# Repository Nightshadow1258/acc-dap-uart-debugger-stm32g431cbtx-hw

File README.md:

# ACC DAP-UART Debugger (STM32G431) – Hardware

A small, low-cost **USB-C debug probe** that combines a **CMSIS-DAP (SWD) debugger** and a **USB-to-UART bridge** in a single USB device. It connects to the target with a 10-pin **Tag-Connect TC2050** cable.

When plugged into a PC, the board shows up as:
- a **CMSIS-DAP v2 probe** (works with OpenOCD, `west flash`, `west debug`, GDB)
- a **virtual COM port** (USB CDC-ACM) that forwards the target's UART

One cable to the PC, one cable to the target.

> **Firmware:** this repository only contains the hardware. The Zephyr RTOS firmware is here:
> [acc-dap-uart-debugger-stm32g431cbtx-fw](https://github.com/Nightshadow1258/acc-dap-uart-debugger-stm32g431cbtx-fw)
>
> **Blog post:** [DIY Debugger: CMSIS-DAP + UART over a Single USB-C Cable](https://blog.preisch.cloud/) <!-- TODO: replace with the post's URL once published -->

---

## Features

| | |
|---|---|
| **MCU** | STM32G431CBT6 (Cortex-M4, 170 MHz, 128 KB Flash, 32 KB RAM, LQFP48) |
| **USB** | USB Type-C, USB 2.0 Full-Speed, crystal-less (internal HSI48) |
| **Power** | Bus-powered from USB 5 V, no external supply |
| **Debug interface** | SWD (SWCLK, SWDIO, NRST) via bit-banged GPIO |
| **UART bridge** | USART2, default 115200 baud |
| **Target connector** | Tag-Connect TC2050 (10-pin, no header needed on the target) |
| **Indicators** | Power LED, status LED |
| **Enclosure** | Two-part 3D-printable case (FreeCAD) |

---

## Repository Structure

```
ACC_DAP-UART-Debugger_STM32G431CBTx/
├── Dokumentation/   # Schematic PDF, images, notes
├── KiCAD/           # KiCad project (ACC_DAP-UART-Debugger_STM32G431CBTx.kicad_pro)
└── FreeCAD/         # Enclosure design (top + bottom part)
```

---

## Target Connector Pinout (TC2050)

Pin names are from the **target MCU's side**.

| Pin Name   | Pin | Pin | Pin Name   |
|------------|:---:|:---:|------------|
| VDD        | 1   | 2   | GND        |
| UART_RXD   | 3   | 4   | UART_TXD   |
| JTMS_SWDIO | 5   | 6   | JTCK_SWCLK |
| JTDO_SWO   | 7   | 8   | JTDI       |
| TBD/Free   | 9   | 10  | JTRST      |

- The target's `UART_RXD` (pin 3) connects to the debugger's **TX**, and the target's `UART_TXD` (pin 4) to the debugger's **RX**.
- Pin 9 is reserved for future use.
- This debugger uses **SWD only**. The JTAG-only pins (`JTDI`, `JTRST`) and `SWO` are part of the connector standard but not used by the current firmware.

To use the debugger with your own board, place the **TC2050-IDC-NL** footprint (no-legs version, or the legged version for retention clips) and route it according to the table above.

---

## MCU Pin Assignment

| Function | MCU Pin | Notes |
|---|---|---|
| Target SWCLK | `PA5` | GPIO, push-pull |
| Target SWDIO | `PA4` | GPIO, pull-up |
| Target NRST  | `PB0` | GPIO |
| Target UART TX | `PA2` | USART2_TX |
| Target UART RX | `PA3` | USART2_RX |
| USB D- / D+ | `PA11` / `PA12` | USB FS |

---

## Enclosure

The case was designed in **FreeCAD** around the STEP model exported from KiCad.

- Two parts (top + bottom)
- Screws go in from the bottom and sit in recessed mounting points
- The top part holds **M2 threaded inserts** and has a cut-out for the TC2050 connector

---

## Getting Started

1. **Order / assemble** the PCB from the files in `KiCAD/`.
2. **Flash the firmware** over USB DFU (STM32 ROM bootloader):
   - hold `BOOT0`, plug in USB, release `BOOT0`
   - flash using the instructions in the [firmware repository](https://github.com/Nightshadow1258/acc-dap-uart-debugger-stm32g431cbtx-fw)
3. **Connect** the TC2050 cable to your target and check that the probe is detected:
   ```bash
   openocd -f interface/cmsis-dap.cfg -f target/stm32f4x.cfg
   ```
4. **Use it in a Zephyr project** by adding this to the target's `board.cmake`:
   ```cmake
   board_runner_args(openocd --config interface/cmsis-dap.cfg --config target/<target>.cfg)
   ```
   then run `west flash --runner openocd`.

### Tested targets
| Target | Status |
|---|---|
| STM32F4 ([Stepper Controller V1.0](https://blog.preisch.cloud/stepper-controller-v1-0/)) | Working |
| nRF52840 ([Sensor Node](https://blog.preisch.cloud/blog-sensor-node-v4-00/)) | Working |
| STM32G4 ([Motor Controller](https://blog.preisch.cloud/diy-motor-controller-part-i-hardware-design-bringup/)), incl. external flash | To test |

---

## License
This hardware design is licensed under the CERN-OHL-P v2

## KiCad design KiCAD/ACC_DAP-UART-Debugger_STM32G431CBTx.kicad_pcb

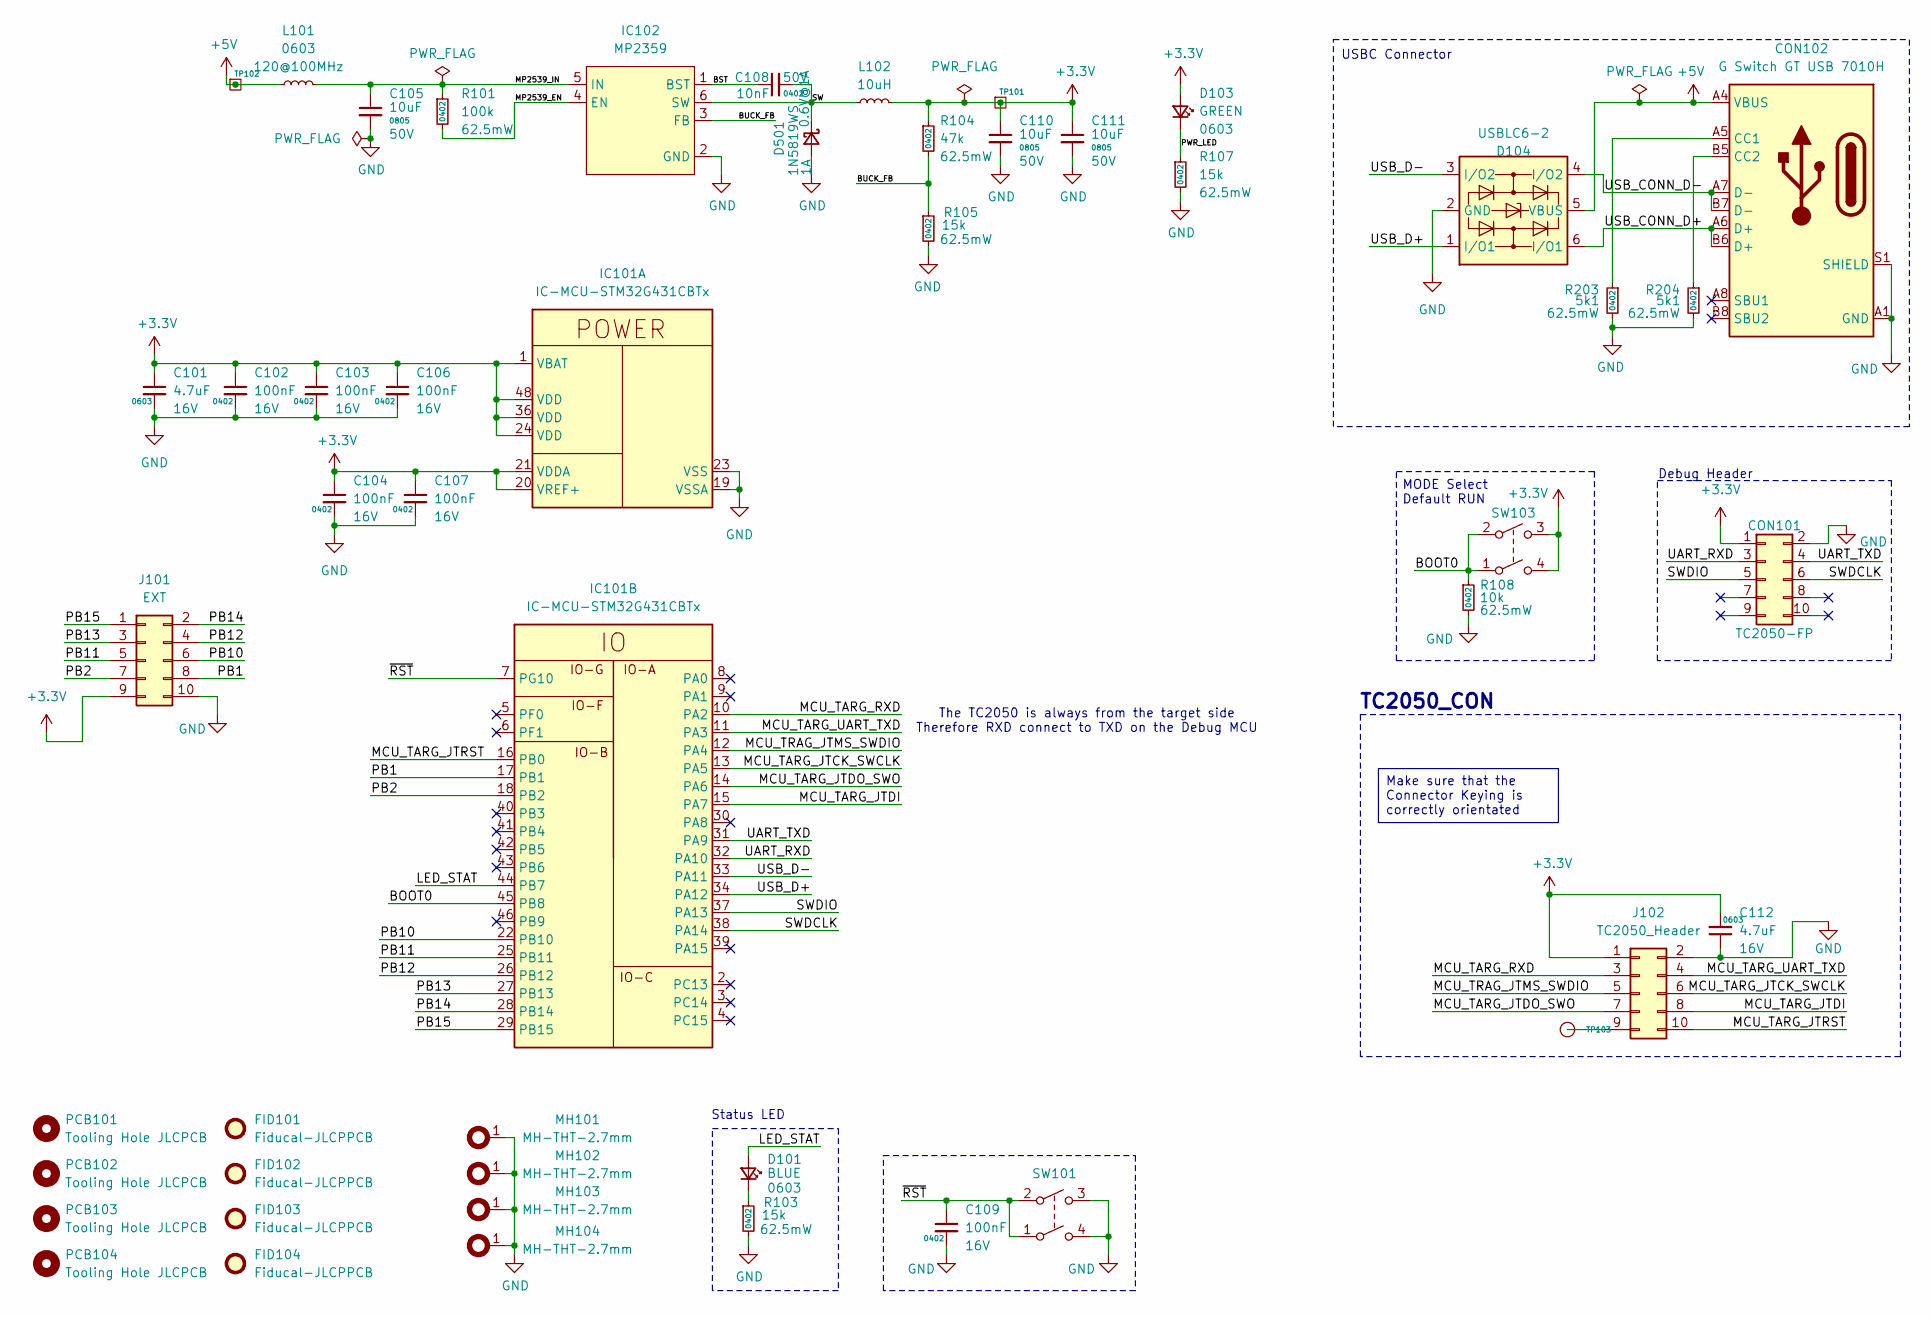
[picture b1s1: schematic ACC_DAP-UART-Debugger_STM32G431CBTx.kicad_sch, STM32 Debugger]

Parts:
C101, C112: 4.7uF; C_0603_1608Metric; Voltage 16V; LCSC Part # C19666
C102, C103, C104, C106, C107, C109: 100nF; C_0402_1005Metric; Voltage 16V; LCSC Part # C1525
C105, C110, C111: 10uF; C_0805_2012Metric; Voltage 50V; LCSC Part # C440198
C108: 10nF; C_0402_1005Metric; Voltage 50V; LCSC Part # C15195
CON101: TC2050-FP; CON-TAG-CONNECT_TC2050-IDC
CON102: G Switch GT USB 7010H; CON-GEN-USB_C-16P; LCSC Part # C2988369
D101: BLUE; D_0603_1608Metric; LCSC Part # C965807
D103: GREEN; D_0603_1608Metric; LCSC Part # C965804
D104: USBLC6-2; SOT-23-6; LCSC Part # C7519
D501: 1N5819WS; D_SOD-323; LCSC Part # C191023
FID101, FID102, FID103, FID104: Fiducal-JLCPPCB; PCB-FID-JLCPCB
IC101: IC-MCU-STM32G431CBTx; LQFP-48_7x7mm_P0.5mm; LCSC Part # C529355
IC102: MP2359; SOT-23-6; LCSC Part # C2959845
J101: EXT; PinHeader_2x05_P2.54mm_Vertical
J102: TC2050_Header; IDC-Header_2x05_P2.54mm_Vertical
L101: FB-BLM18PG121SN1; L_0603_1608Metric; LCSC Part # C14709
L102: 10uH; L_SXN_SMNR4020; LCSC Part # C135263
MH101, MH102, MH103, MH104: MH-THT-2.7mm; MountingHole_2.7mm_Pad_Via
PCB101, PCB102, PCB103, PCB104: Tooling Hole JLCPCB; PCB-NPTH-JLCPCB
R101: 100k; R_0402_1005Metric; Power Rating 62.5mW; LCSC Part # C25741
R103, R105, R107: 15k; R_0402_1005Metric; Power Rating 62.5mW; LCSC Part # C25756
R104: 47k; R_0402_1005Metric; Power Rating 62.5mW; LCSC Part # C25792
R108: 10k; R_0402_1005Metric; Power Rating 62.5mW; LCSC Part # C25744
R203, R204: 5k1; R_0402_1005Metric; Power Rating 62.5mW; LCSC Part # C25905
SW101, SW103: SW-GEN-TS-1187A; SW-PUSH-DPST-XKS-TS-1187A; LCSC Part # C318884
TP101, TP102: Testpoint-BASE; TP_THT_D0.8mm
TP103: TP; TP_Pad_D0.9mm

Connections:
+3.3V: C101.1, C102.1, C103.1, C104.1, C106.1, C107.1, C110.1, C111.1, C112.2, CON101.1, D103.2 (A), IC101.1 (VBAT), IC101.20 (VREF+), IC101.21 (VDDA), IC101.24 (VDD), IC101.36 (VDD), IC101.48 (VDD), J101.9, J102.1, L102.2, R104.1, SW103.3 (4), SW103.4, TP101.1
+5V: CON102.A4 (VBUS), CON102.A9 (VBUS), CON102.B4 (VBUS), CON102.B9 (VBUS), D104.5 (VBUS), L101.1, TP102.1
/BOOT0: IC101.45 (PB8), R108.1, SW103.1, SW103.2 (3)
/BST: C108.1, IC102.1 (BST)
/BUCK_FB: IC102.3 (FB), R104.2, R105.1
/LED_STAT: D101.2 (A), IC101.44 (PB7)
/MCU_TARG_JTCK_SWCLK: IC101.13 (PA5), J102.6
/MCU_TARG_JTDI: IC101.15 (PA7), J102.8
/MCU_TARG_JTDO_SWO: IC101.14 (PA6), J102.7
/MCU_TARG_JTRST: IC101.16 (PB0), J102.10
/MCU_TARG_RXD: IC101.10 (PA2), J102.3
/MCU_TARG_UART_TXD: IC101.11 (PA3), J102.4
/MCU_TRAG_JTMS_SWDIO: IC101.12 (PA4), J102.5
/MP2539_EN: IC102.4 (EN), R101.2
/MP2539_IN: C105.1, IC102.5 (IN), L101.2, R101.1
/PB1: IC101.17 (PB1), J101.8
/PB2: IC101.18 (PB2), J101.7
/PB10: IC101.22 (PB10), J101.6
/PB11: IC101.25 (PB11), J101.5
/PB12: IC101.26 (PB12), J101.4
/PB13: IC101.27 (PB13), J101.3
/PB14: IC101.28 (PB14), J101.2
/PB15: IC101.29 (PB15), J101.1
/PWR_LED: D103.1 (K), R107.1
/SW: C108.2, D501.1 (K), IC102.6 (SW), L102.1
/SWDCLK: CON101.6, IC101.38 (PA14)
/SWDIO: CON101.5, IC101.37 (PA13)
/UART_RXD: CON101.3, IC101.32 (PA10)
/UART_TXD: CON101.4, IC101.31 (PA9)
/USB_CONN_D+: CON102.A6 (D+), CON102.B6 (D+), D104.6 (I/O1)
/USB_CONN_D-: CON102.A7 (D-), CON102.B7 (D-), D104.4 (I/O2)
/USB_D+: D104.1 (I/O1), IC101.34 (PA12)
/USB_D-: D104.3 (I/O2), IC101.33 (PA11)
/~RST: C109.1, IC101.7 (PG10), SW101.1, SW101.2 (3)
GND: C101.2, C102.2, C103.2, C104.2, C105.2, C106.2, C107.2, C109.2, C110.2, C111.2, C112.1, CON101.2, CON102.A1 (GND), CON102.A12 (GND), CON102.B1 (GND), CON102.B12 (GND), CON102.S1 (SHIELD), D104.2 (GND), D501.2 (A), IC101.19 (VSSA), IC101.23 (VSS), IC101.35 (VSS), IC101.47 (VSS), IC102.2 (GND), J101.10, J102.2, MH101.1, MH102.1, MH103.1, MH104.1, R103.2, R105.2, R107.2, R108.2, R203.2, R204.2, SW101.3 (4), SW101.4
unnamed: CON102.A5 (CC1), R203.1
unnamed: CON102.B5 (CC2), R204.1
unnamed: D101.1 (K), R103.1
unnamed: J102.9, TP103.1

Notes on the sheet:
MODE Select Default RUN
USBC Connector
Debug Header
Status LED
The TC2050 is always from the target side Therefore RXD connect to TXD on the Debug MCU
TC2050_CON
Make sure that the Connector Keying is correctly orientated

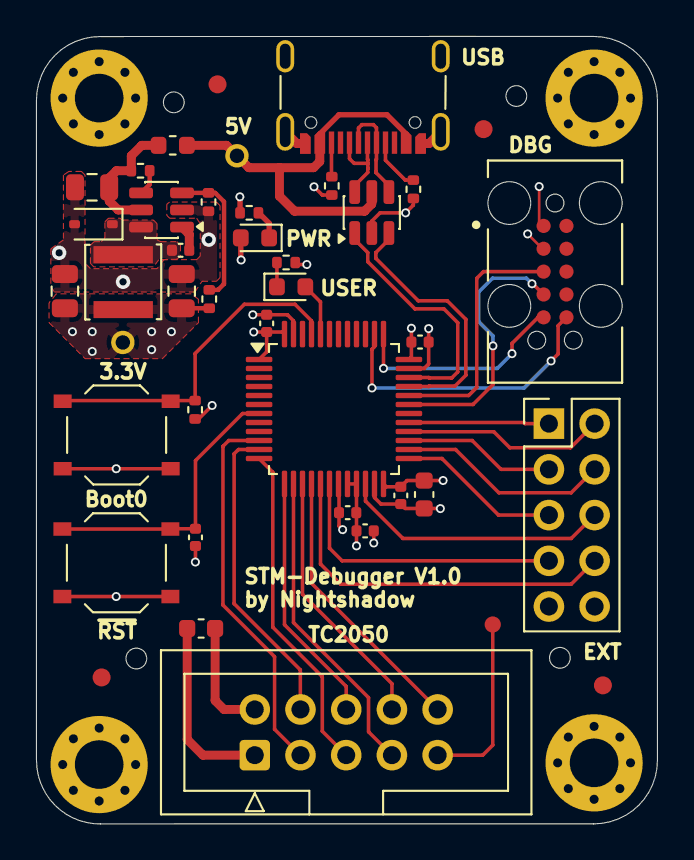
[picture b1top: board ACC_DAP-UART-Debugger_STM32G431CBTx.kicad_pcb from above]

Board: 4 copper layers, 34.5 x 43.7 mm, 49 parts (0 on the bottom side), 39 nets.

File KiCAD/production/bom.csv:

Designator,Footprint,Quantity,Value,LCSC Part #
"C101, C112",0603,2,4.7uF,C19666
"C102, C103, C104, C106, C107, C109",0402,6,100nF,C1525
"C105, C110, C111",0805,3,10uF,C440198
C108,0402,1,10nF,C15195
CON102,CON-GEN-USB_C-16P,1,G Switch GT USB 7010H,C2988369
D101,0603,1,BLUE,C965807
D103,0603,1,GREEN,C965804
D104,SOT-23-6,1,USBLC6-2,C7519
D501,D_SOD-323,1,1N5819WS,C191023
IC101,LQFP-48_7x7mm_P0.5mm,1,IC-MCU-STM32G431CBTx,C529355
IC102,SOT-23-6,1,MP2359,C2959845
J101,PinHeader_2x05_P2.54mm_Vertical,1,EXT,
J102,IDC-Header_2x05_P2.54mm_Vertical,1,TC2050_Header,
L101,0603,1,FB-BLM18PG121SN1,C14709
L102,L_SXN_SMNR4020,1,10uH,    C135263
R101,0402,1,100k,C25741
"R103, R105, R107",0402,3,15k,C25756
R104,0402,1,47k,C25792
R108,0402,1,10k,C25744
"R203, R204",0402,2,5k1,C25905
"SW101, SW103",SW-PUSH-DPST-XKS-TS-1187A,2,SW-GEN-TS-1187A,C318884

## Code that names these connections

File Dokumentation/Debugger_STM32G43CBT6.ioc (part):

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Mcu.Name=STM32G431C(6-8-B)Tx
Mcu.Package=LQFP48
Mcu.UserName=STM32G431CBTx
PA10.Mode=Asynchronous
PA10.Signal=USART1_RX
PA11.Mode=Device
PA11.Signal=USB_DM
PA12.Mode=Device
PA12.Signal=USB_DP
PA13.Mode=Serial_Wire
PA13.Signal=SYS_JTMS-SWDIO
PA14.Mode=Serial_Wire
PA14.Signal=SYS_JTCK-SWCLK
PA2.GPIOParameters=GPIO_Label
PA2.GPIO_Label=TRAG_USART2_TX
PA2.Mode=Asynchronous
PA2.Signal=USART2_TX
PA3.GPIOParameters=GPIO_Label
PA3.GPIO_Label=TRAG_USART2_RX
PA3.Mode=Asynchronous
PA3.Signal=USART2_RX
PA4.GPIOParameters=GPIO_Label
PA4.GPIO_Label=TRAG_SWDIO
PA4.Signal=GPIO_Output
PA5.GPIOParameters=GPIO_Label
PA5.GPIO_Label=TRAG_SWCLK
PA5.Signal=GPIO_Output
PA6.GPIOParameters=GPIO_Label
PA6.GPIO_Label=TRAG_SWO
PA6.Signal=GPIO_Output
PA7.GPIOParameters=GPIO_Label
PA7.GPIO_Label=TRAG_JTDI
PA7.Signal=GPIO_Output
PA9.Mode=Asynchronous
PA9.Signal=USART1_TX
PB0.GPIOParameters=GPIO_Label
PB0.GPIO_Label=TRAG_JTRST
PB0.Signal=GPIO_Output
PB1.Signal=GPIO_Output
PB10.Signal=GPIO_Output
PB11.Signal=GPIO_Output
PB12.Signal=GPIO_Output
PB13.Signal=GPIO_Output
PB14.Signal=GPIO_Output
PB15.Signal=GPIO_Output
PB2.Signal=GPIO_Output
PB8-BOOT0.GPIOParameters=GPIO_Label
PB8-BOOT0.GPIO_Label=BOOT0
PB8-BOOT0.Signal=GPIO_Input
PG10-NRST.GPIOParameters=GPIO_Label
PG10-NRST.GPIO_Label=NRST
PG10-NRST.Signal=GPIO_Input
RCC.HSE_VALUE=8000000
RCC.SYSCLKFreq_VALUE=170000000
RCC.SYSCLKSource=RCC_SYSCLKSOURCE_PLLCLK
board=custom
